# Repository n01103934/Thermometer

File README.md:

# Build Instructions

# Introduction
My project I am working with deals with reading temperature data from a temperature sensor. My sensor 
is called a TMP006 IR Temperature Sensor that can measure the temperature of any object without making direct contact with it.
It detects and absorbs the infrared energy from an object regardless of how hot or cold it is. I plan on storing 
my temperature data from my sensor to the Firebase database where all my data is stored. The reason why I chose this
project is because I was interested in the idea of reading an object's temperature data from the sensor just by pointing my finger
directly close to it. Here is a system UML diagram below to show you how my hardware will send data from my Raspberry Pi 3 to my database.

# Bill of Materials/Budget
The total cost of my budget is $131.55 which is below the maximum limit of $150. I did not order any of my hardware materials online instead I went to local electronic stores such as Canada Computers and Creatron Inc. They had everything I needed in my budget including Raspberry Pi 3 kit, TMP006 IR Temperature Sensor, SD Card, USB to Ethernet Adapter, etc. I also included where I got my parts from the links in my budget. Here is a image below to show you my budget and all the materials I used for my project.

# Time Commitment
The project did not take me long to complete because I got my parts ahead of time and started working on it as soon as possible.
However, their was still alot of time and commitment put in setting up my Raspberry Pi 3 and changing the default address to the
address you are assigned as well as reading data from the sensor. If you got all your materials then it would take you about 3 to 5 weeks to complete the project as long as you follow the steps of building it. Their are electronic stores that lucky have what you need such as Creatron Inc and Canada Computers. Once you acquired the parts start setting up your Raspberry Pi 3 which took almost a week at the lastest for me to set it up. After that then solder the header pins with the sensor to make a connection to it and the Raspberry Pi 3. Then, test the sensor and see if it can read data by running the python program for the sensor's library and it should be able to display the temperature readings on the output just by pointing finger close to the sensor. Overall, it took alot of time and commitment inorder to finish this project and put it all together for the next term.

# Mechanical Assembly
Before, you connect your sensor to Raspberry Pi 3 you need to get header pins in order for your Raspberry Pi 3 to detect it. I provided 
a link to show you where you could get them for your sensor incase you don't already have one.  
https://www.digikey.ca/product-detail/en/omron-electronics-inc-emc-div/XG8T-0231/XG8T-0231-ND/1829453?utm_adgroup=&mkwid=s3xcZrPTl&pcrid=312348616043&pkw=&pmt=&pdv=c&productid=1829453&slid=&gclid=EAIaIQobChMIp6fskvWQ3wIVFHdeCh2qPAeFEAYYASABEgKKKvD_BwE

This open-sourced adafruit website will help you connect the TMP006 IR Temperature Sensor with the Raspberry Pi 3 or BeagleBone Black.
https://learn.adafruit.com/tmp006-temperature-sensor-python-library/hardware

Firstly, you need to connect a jumper wire from the 3.3V pin of the Raspberry Pi 3 to first pin(VCC) on my sensor. Secondly, the GND pin on Raspberry Pi 3 connects another jumper wire to the second pin(GND) of my sensor. After, connect a third jumper wire from SDA pin of Raspberry Pi 3 to the third pin(SDA) of my sensor. Then, the SCL pin of Raspberry Pi 3 connects with the fourth pin(SCL) of my sensor. The next link will give you information on how to change your sensor's default address which is 0x40 to another one ranging from 0x41 to 0x47. https://learn.adafruit.com/infrared-thermopile-sensor-breakout/assembly-and-wiring

# PCB / Soldering
I made a fritzing file in my repository to create my own custom PCB just by following my breadboard and schematic
connections to do the same for the PCB. The file is called Thermometer Circuit Diagram.fzz in my github repository. 
https://github.com/n01103934/Thermometer

Here are images below to view my breadboard, schematic, and pcb diagrams for my project.

Additionally, I emailed the prototype lab my gerber files by exporting them from my fritzing project and got my board 
the next day. Then, I started soldering my via traces on my custom PCB and connected my header pins to the board. 
After, I soldered my header pins on sensor to my PCB board from the top to bottom and I connected the header socket to 
my board as well. I had to solder a wire connecting from the GND pin to my via trace connected to ground in order for my Raspberry Pi 3 to have a solid connection with my sensor. Finally, I connected the PCB to my Raspberry Pi 3, powered it on, ran the sudo i2cdetect -y 1 on cmd
terminal and I got my I2C address (0x46) displayed on the output for my sensor. 

# Power Up
First you need to download the operating system of Pi and format the micro SD card using the SD card reader included with 
the card to upload the Pi image to the Raspberry Pi 3. Here is a very useful blog that I followed step by step to upload my 
image to Raspberry Pi 3 as well as basic setup. https://github.com/six0four/StudentSenseHat/blob/master/cribpisdcard.md

Once you installed the operating system and got the image uploaded to Raspberry Pi 3, insert the SD card into the slot at the 
bottom of Pi, and boot it up with the power supply. If you are booting the Raspberry Pi 3 for the first time then you will have 
the option to change the default username and password to what ever suits you or you can leave it the same. The default username 
and password for every Raspberry Pi is always pi and raspberry unless a user changes it. Everything you need to know about the basic
setup of the Raspberry Pi is from the first link provided above just follow the instructions and your Pi should be ready. Some commands
to consider using for updating your Raspberry Pi 3 are sudo apt-get update and sudo apt-get dist-upgrade for installing packages to their latest versions for Pi. You need to make sure that I2C is enabled on the Raspberry Pi in order to use cmds like i2c detect for displaying the address of your sensor. In order to do that go to the Raspberry Pi configuration from start menu or type in terminal sudo raspi-config, then go to Interfaces and click on the I2C option to enable it if it hasn't already been enabled yet. 

Here is an image below to demonstrate me powering up my Raspberry Pi 3 with PCB connected to it.

# Unit Testing
In order to test whether or not the sensor is connected to the Raspberry Pi 3 properly you need to
open up a terminal on Pi and issue the command sudo i2cdetect -y 1 to list all the I2C addresses connected to the
Raspberry Pi 3. Here is an image below to show you my I2C address shown in the output screen.

Additionally, once you see your address listed on the output now we can test the sensor by running
the python program from adafruit website. Follow the instructions on the adafruit website to install the python library
into Raspberry Pi 3 to run the simpletest.py that came with adafruit library for reading data from the sensor. The program
can be found in my github repository called simpletest.py and to compile/run it type in sudo python simpletest.py. This command 
will not only compile it but run the python program if there are no errors in the file and after entering it the program will
execute to display the temperature readings every second. 

I have provided a link below to the open-sourced adafruit website which will show you step by step how to make the sensor read data by running the python program in terminal. https://learn.adafruit.com/tmp006-temperature-sensor-python-library/software 

# Production Testing
When the python program ran successfully, it displayed the temperature from the sensor itself 
and object temperature just by pointing my finger towards it. The temperature readings prints
out every second and change based on me putting my hand close to it and far from it. 
The program is running on an infinite loop so you don't need to keep running it again and again
to see if the temperature values are changing. 

# Reproducible
Yes

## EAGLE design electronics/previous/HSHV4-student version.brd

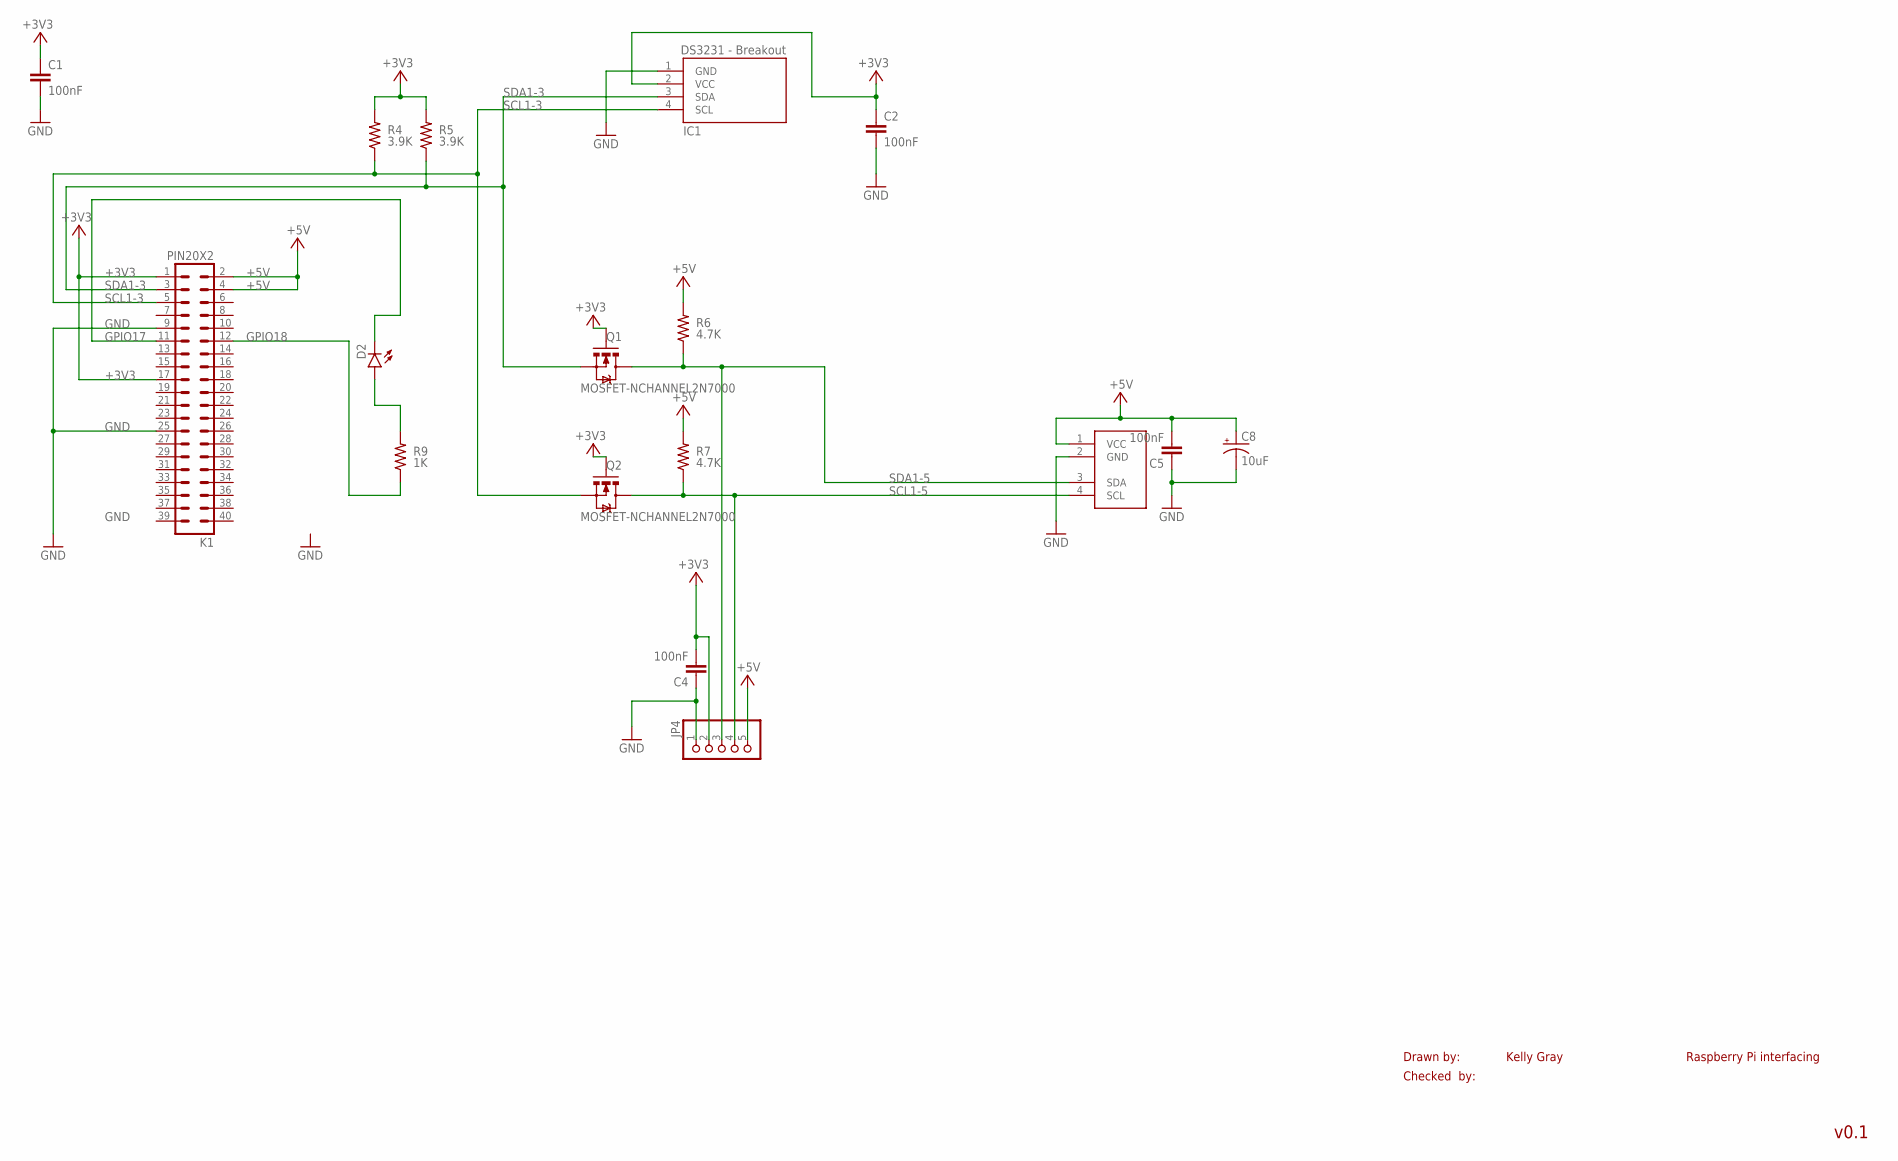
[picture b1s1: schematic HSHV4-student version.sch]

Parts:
C1, C2, C4, C5: 100nF; CAP-PTH-SMALL-KIT
C8: 10uF; CPOL-RADIAL-10UF-25V
D2: LED-3MM-NO_SILK; LED3MM-NS
IC1: DS3231; 8PTH
JP4: PINHD-1X5; 1X05
K1: PIN20X2; PIN_20X2
Q1, Q2: MOSFET-NCHANNEL2N7000; TO-92
R4, R5: 3.9K; AXIAL-0.3; TOLERANCE 5%
R6, R7: 4.7K; AXIAL-0.3; TOLERANCE 5%
R9: 1K; AXIAL-0.3; TOLERANCE 5%
U$1: PCF8591; 1X04

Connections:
+3V3: C1.1, C2.1, C4.2, IC1.2 (VCC), JP4.2, K1.1, K1.17, Q1.2 (G), Q2.2 (G), R4.P$2 (2), R5.P$2 (2)
+5V: C5.2, C8.1 (+), JP4.5, K1.2, K1.4, R6.P$2 (2), R7.P$2 (2), U$1.1 (VCC)
GND: C1.2, C2.2, C4.1, C5.1, C8.2 (-), IC1.1 (GND), JP4.1, K1.9, K1.25, U$1.2 (GND)
GPIO17: D2.K (C), K1.11
GPIO18: K1.12, R9.P$1 (1)
unnamed: D2.A, R9.P$2 (2)
SCL1-3: IC1.4 (SCL), K1.5, Q2.1 (S), R4.P$1 (1)
SCL1-5: JP4.4, Q2.3 (D), R7.P$1 (1), U$1.4 (SCL)
SDA1-3: IC1.3 (SDA), K1.3, Q1.1 (S), R5.P$1 (1)
SDA1-5: JP4.3, Q1.3 (D), R6.P$1 (1), U$1.3 (SDA)

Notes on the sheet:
Drawn by:
Checked by:
Kelly Gray
v0.1
Raspberry Pi interfacing

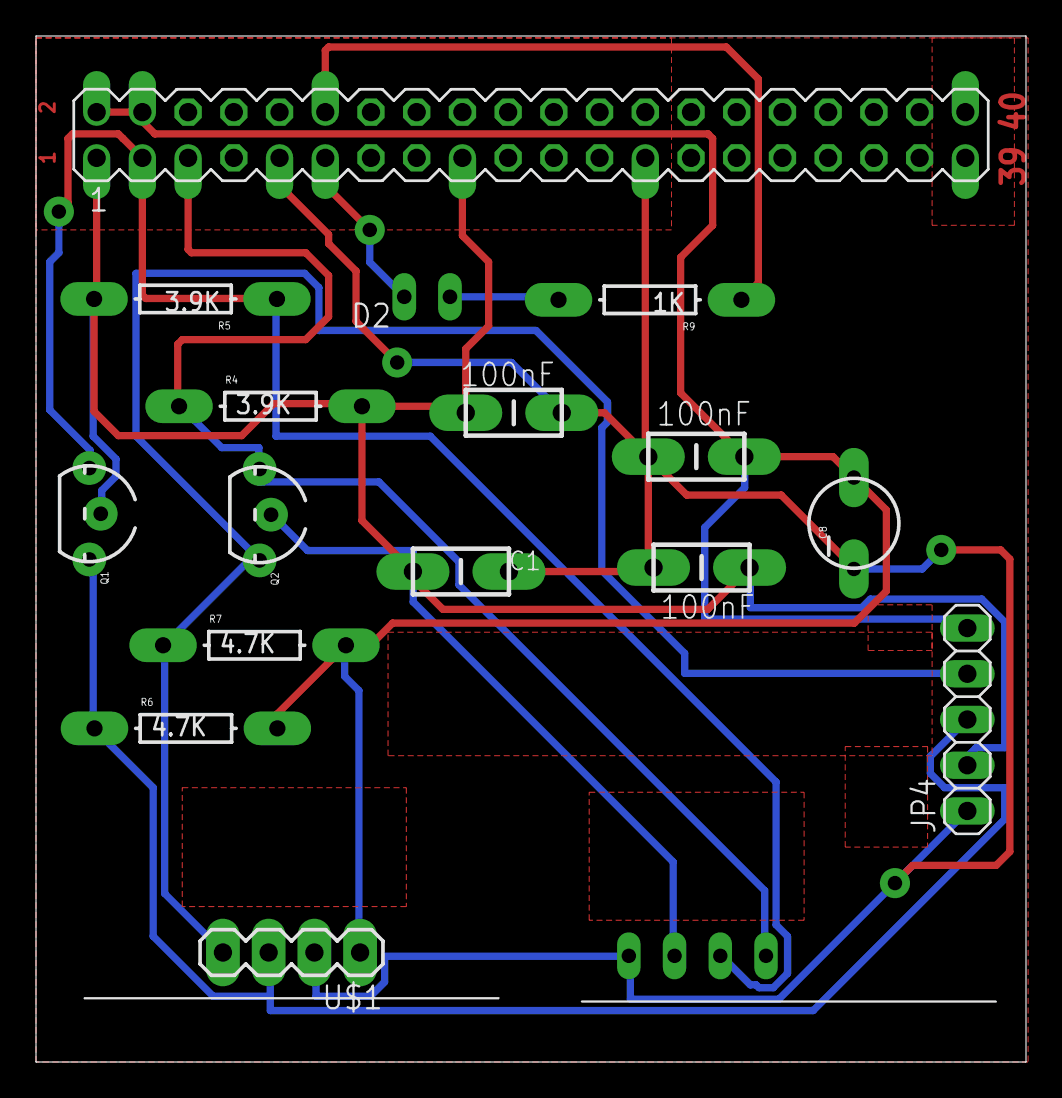
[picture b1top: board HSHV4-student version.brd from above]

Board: 2 copper layers, 55.0 x 57.0 mm, 17 parts (0 on the bottom side), 10 nets.

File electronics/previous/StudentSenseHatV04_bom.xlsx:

Part | Description | Quantity | Package | Value | Supplier | Reference Number | Cost (1) | Cost (60) | Subtotal (1 kit) | Subtotal (60 kits)
JP4 | 1x4 Header (Female) | 3 | PTH | PIN1x4 | Digikey | S1012E-04-ND | 1.7 | 102 | 5.0999999999999996 | 306
K1 | 2x20 Header (Female) | 1 | PTH |  | Digikey | S6104-ND | 3.73 | 223.8 | 3.73 | 223.8
R9 | 1kΩ Resistor | 1 | PTH | 1kΩ | Digikey | CF14JT1K00CT-ND | 0.15 | 9 | 0.15 | 9
R4,R5 | 3.9kΩ Resistor | 2 | PTH | 3.9kΩ | Digikey | CF14JT3K90CT-ND | 0.6 | 36 | 1.2 | 72
R6,R7 | 4.7kΩ Resistor | 2 | PTH | 4.7kΩ | Digikey | CF14JT4K70CT-ND | 0.45 | 27 | 0.9 | 54
D2 | Two colour LED | 1 | PTH | 3mm | Digikey | 1497-1025-ND | 0.61 | 36.6 | 0.61 | 36.6
IC1 | Real Time Clock (I2C) | 1 | Breakout | DS3231 | Creatron | PRORT-003231 | 11.95 | 717 | 11.95 | 717
Q1,Q2 | N-Channel Logic Level MOSFET | 2 | TO-92 | 2N7000 | Creatron | TRFET-007000 | 1.5 | 90 | 3 | 180
U$1 | 8-bit I2C ADC&DAC w/ sensors | 1 | Breakout | PCF8591 | Creatron | PRODA-008591 | 8.5 | 510 | 8.5 | 510
 |  |  |  |  |  | TOTAL |  |  | 35.14 | 2108.4

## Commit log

2018-12-11 Build Instructions

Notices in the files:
parts and their libraries:
SparkFun-Resistors: Licensing: Creative Commons ShareAlike 4.0 International - https://creativecommons.org/licenses/by-sa/4.0
